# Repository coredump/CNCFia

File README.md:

# CNCFia

The idea with this board is to provide a *generic* shield/daughter card for 3.3V MCUs running CNC firmwares like GRBL (and its ports) and g2core. For that, instead of making a shield with specific sockets, we decided to provide a pin header that can be used to connect to different MCUs.

## Included capabilities

### Switches

There are six opto-isolated connectors for limit switches (X, Y, and Z Min/Max limits), a Probe connector and an extra opto-isolated connector to be used for any generic function, and five non-opto isolated ones to be used for external controls (Door security, Emergency Stop, etc).

The opto-isolated switches have an option to be powered by an entirely separated power source to provide full electrical isolation.

All the switches are pulled UP via 4.7kΩ resistors, intended to be used with NC (normally closed) switches connected to the GND, making it an active low signal. Take that in consideration when wiring/configuring the software.

### External driver control/level shifting

Support for nine voltage shifted outputs, mosfet (2n700X) driven. Enough to provide Step/Pulse/Enable signals for three external drivers (those usually have a 5V control voltage).

The mosfets connect the outputs to GND, so when wiring make sure to provide the 5V common wire to all positive (+) signals and the outputs to the negative (-) signals.

TODO example

## Jumper Settings

|  JP1  | Result                                                                                                   |
| :---: | -------------------------------------------------------------------------------------------------------- |
|  1-2  | 5V voltage for board functions will be provided by external power source connected to **EXTERNAL 5V IN** |
|  1-3  | 5V to board functions will be provided by the MCU 5V Pin connected to the controller input               |

## Connector Descriptions

TODO add descriptions and image

## Electrical notes

View this project on [CADLAB.io](https://cadlab.io/project/2459).

All calculations were made considering a 3.3V output from the driving MCU pins, while keeping the output currents under 10 mA, what should be safe for most of the MCUs around.

The 3904s driving the relays have a base current (Ib) of ~ 7.8 mA, that should be enough to saturate the transistor and provide the 78 mA needed by the relay coil.

The LTV-847s are used with typical values for Vf and If, according to datasheet specs.

The OPAMP output for the spindle can be regulated with a potentiometer and from the 3.3V PWM it can get values close to 11V with a 12V power source. Simulated circuit shows a 0.4s approximately time to get to the stable voltage.

## License, Copyright and disclaimers

Copyright Jose Junior <jose.junior@gmail.com> 2020.  

This documentation describes Open Hardware and is licensed under the
CERN OHL v. 1.2.  

You may redistribute and modify this documentation under the terms of the
[CERN OHL v.1.2.](http://ohwr.org/cernohl) This documentation is distributed
**WITHOUT ANY EXPRESS OR IMPLIED WARRANTY, INCLUDING OF
MERCHANTABILITY, SATISFACTORY QUALITY AND FITNESS FOR A
PARTICULAR PURPOSE**. Please see the CERN OHL v.1.2 for applicable
conditions.

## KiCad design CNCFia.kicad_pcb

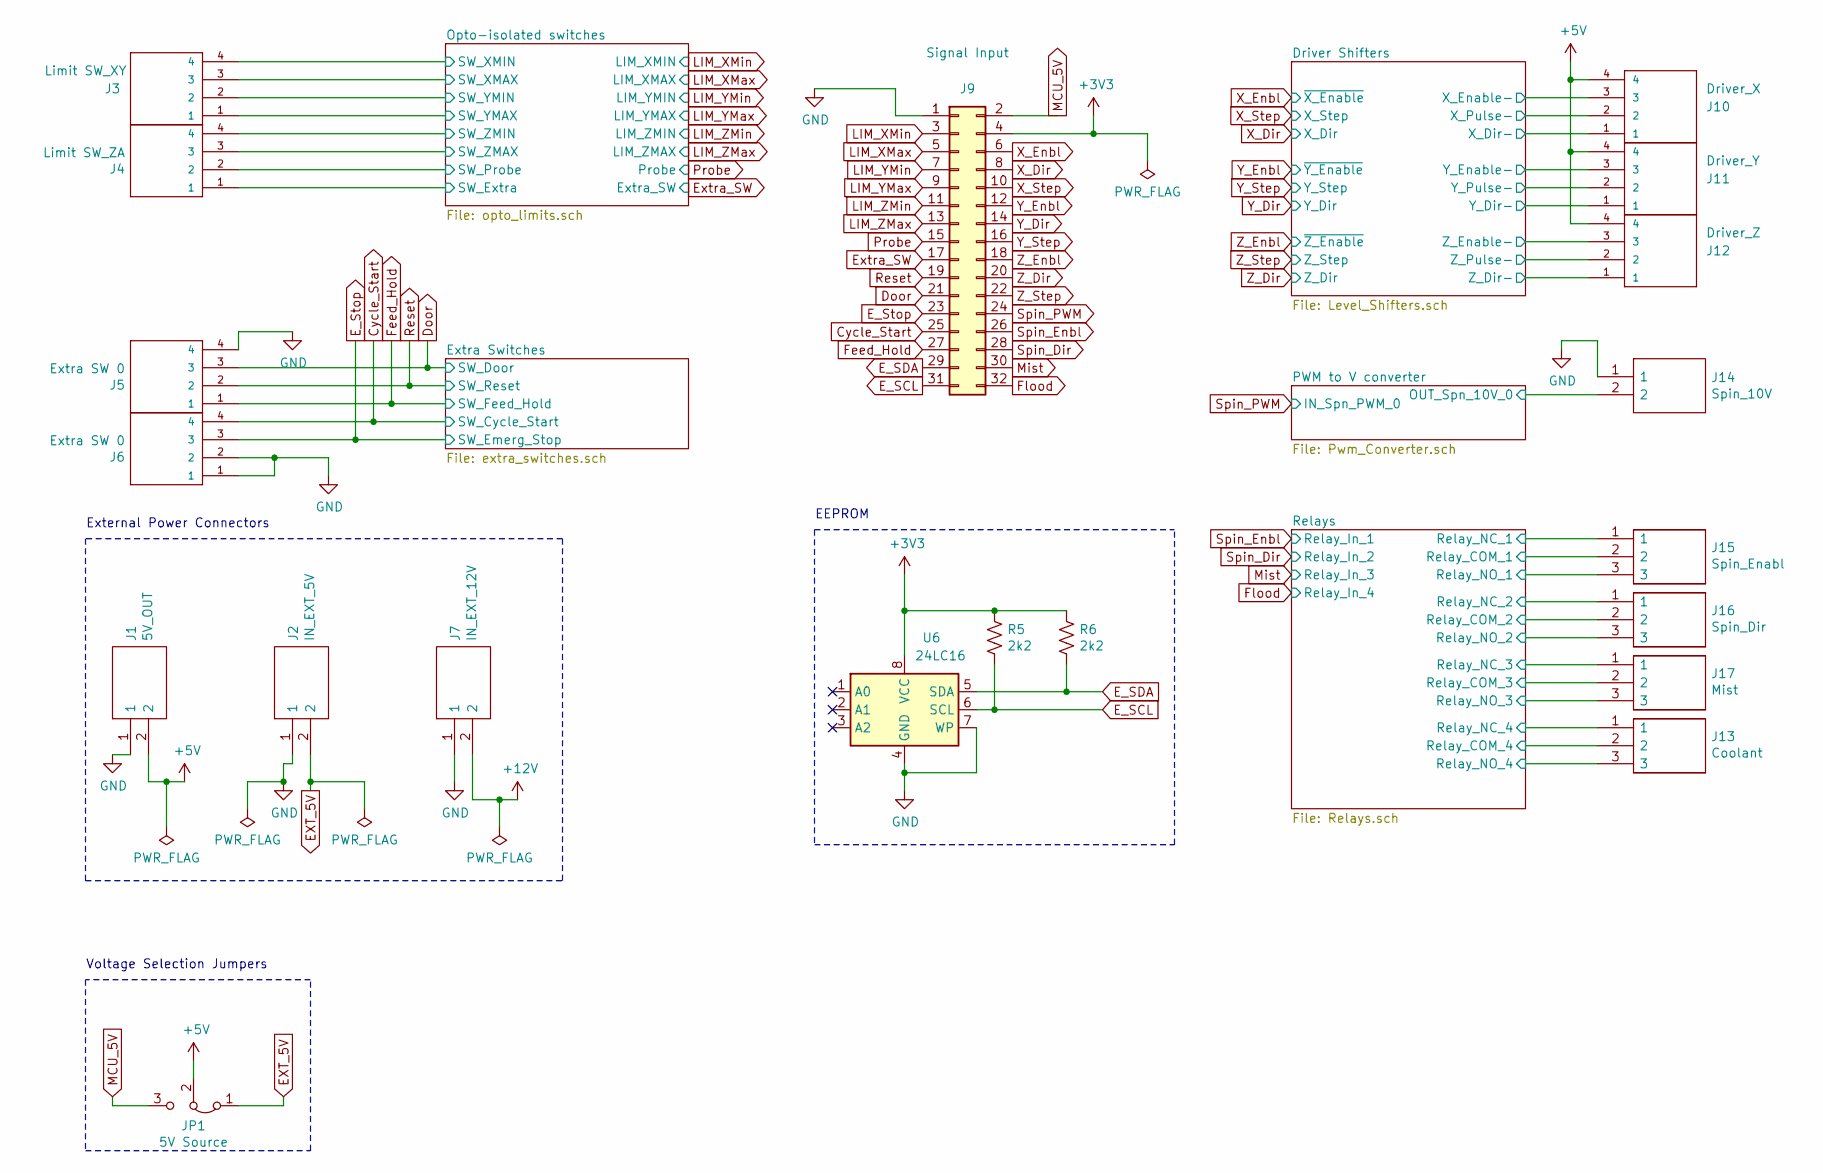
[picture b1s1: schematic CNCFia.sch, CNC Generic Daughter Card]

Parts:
J1: 5V_OUT; CUI_TBP02R2-381-02BE; Mouser Part Number 490-TB008A-508-02BE
J2: IN_EXT_5V; CUI_TBP02R2-381-02BE; Mouser Part Number 490-TB008A-508-02BE
J3: Limit SW_XY; CUI_TBP02R2-381-04BE; MPN TBP01R2-508-04BE; Digi-Key_PN 102-6424-ND
J4: Limit SW_ZA; CUI_TBP02R2-381-04BE; MPN TBP01R2-508-04BE; Digi-Key_PN 102-6424-ND
J5, J6: Extra SW 0; CUI_TBP02R2-381-04BE; MPN TBP01R2-508-04BE; Digi-Key_PN 102-6424-ND
J7: IN_EXT_12V; CUI_TBP02R2-381-02BE; Mouser Part Number 490-TB008A-508-02BE
J9: Signal Input; PinHeader_2x16_P2.54mm_Vertical; MPN 302-S401; Digi-Key_PN ED10529-ND
J10: Driver_X; CUI_TBP02R2-381-04BE; Mouser Part Number 490-TB008A-508-03BE
J11: Driver_Y; CUI_TBP02R2-381-04BE; Mouser Part Number 490-TB008A-508-03BE
J12: Driver_Z; CUI_TBP02R2-381-04BE; Mouser Part Number 490-TB008A-508-03BE
J13: Coolant; CUI_TBP02R2-381-03BE; Mouser Part Number 490-TB008A-508-03BE
J14: Spin_10V; CUI_TBP02R2-381-02BE; Mouser Part Number 490-TB008A-508-02BE
J15: Spin_Enabl; CUI_TBP02R2-381-03BE; Mouser Part Number 490-TB008A-508-03BE
J16: Spin_Dir; CUI_TBP02R2-381-03BE; Mouser Part Number 490-TB008A-508-03BE
J17: Mist; CUI_TBP02R2-381-03BE; Mouser Part Number 490-TB008A-508-03BE
JP1: 5V Source; PinHeader_1x03_P2.54mm_Vertical
R5, R6: 2k2; R_0805_2012Metric_Pad1.15x1.40mm_HandSolder; MPN CRGCQ1206F2K2; Digi-Key_PN A129814CT-ND
U6: 24LC16; SOIC-8_3.9x4.9mm_P1.27mm

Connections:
+5V: J1.2, J10.4, J11.4, J12.4, JP1.2 (C); also elsewhere on the board
+12V: J7.2; also elsewhere on the board
/OUT_Spn_10V_0: J14.2; also elsewhere on the board
/Relay_COM_1: J15.2; also elsewhere on the board
/Relay_COM_2: J16.2; also elsewhere on the board
/Relay_COM_3: J17.2; also elsewhere on the board
/Relay_COM_4: J13.2; also elsewhere on the board
/Relay_NC_1: J15.1; also elsewhere on the board
/Relay_NC_2: J16.1; also elsewhere on the board
/Relay_NC_3: J17.1; also elsewhere on the board
/Relay_NC_4: J13.1; also elsewhere on the board
/Relay_NO_1: J15.3; also elsewhere on the board
/Relay_NO_2: J16.3; also elsewhere on the board
/Relay_NO_3: J17.3; also elsewhere on the board
/Relay_NO_4: J13.3; also elsewhere on the board
/SW_Extra: J4.1; also elsewhere on the board
/SW_Probe: J4.2; also elsewhere on the board
/SW_XMAX: J3.3; also elsewhere on the board
/SW_XMIN: J3.4; also elsewhere on the board
/SW_YMAX: J3.1; also elsewhere on the board
/SW_YMIN: J3.2; also elsewhere on the board
/SW_ZMAX: J4.3; also elsewhere on the board
/SW_ZMIN: J4.4; also elsewhere on the board
/X_Dir-: J10.1; also elsewhere on the board
/X_Enable-: J10.3; also elsewhere on the board
/X_Pulse-: J10.2; also elsewhere on the board
/Y_Dir-: J11.1; also elsewhere on the board
/Y_Enable-: J11.3; also elsewhere on the board
/Y_Pulse-: J11.2; also elsewhere on the board
/Z_Dir-: J12.1; also elsewhere on the board
/Z_Enable-: J12.3; also elsewhere on the board
/Z_Pulse-: J12.2; also elsewhere on the board
Cycle_Start: J6.4, J9.25; also elsewhere on the board
Door: J5.3, J9.21; also elsewhere on the board
EXT_5V: J2.2, JP1.1 (A)
E_SCL: J9.31, R5.2, U6.6 (SCL)
E_SDA: J9.29, R6.2, U6.5 (SDA)
E_Stop: J6.3, J9.23; also elsewhere on the board
Extra_SW: J9.17; also elsewhere on the board
Feed_Hold: J5.1, J9.27; also elsewhere on the board
Flood: J9.32; also elsewhere on the board
GND: J1.1, J2.1, J5.4, J6.1, J6.2, J7.1, J9.1, J14.1, U6.4 (GND), U6.7 (WP); also elsewhere on the board
LIM_XMax: J9.5; also elsewhere on the board
LIM_XMin: J9.3; also elsewhere on the board
LIM_YMax: J9.9; also elsewhere on the board
LIM_YMin: J9.7; also elsewhere on the board
LIM_ZMax: J9.13; also elsewhere on the board
LIM_ZMin: J9.11; also elsewhere on the board
MCU_5V: J9.2, JP1.3 (B)
Mist: J9.30; also elsewhere on the board
Probe: J9.15; also elsewhere on the board
Reset: J5.2, J9.19; also elsewhere on the board
Spin_Dir: J9.28; also elsewhere on the board
Spin_Enbl: J9.26; also elsewhere on the board
Spin_PWM: J9.24; also elsewhere on the board
X_Dir: J9.8; also elsewhere on the board
X_Enbl: J9.6; also elsewhere on the board
X_Step: J9.10; also elsewhere on the board
Y_Dir: J9.14; also elsewhere on the board
Y_Enbl: J9.12; also elsewhere on the board
Y_Step: J9.16; also elsewhere on the board
Z_Dir: J9.20; also elsewhere on the board
Z_Enbl: J9.18; also elsewhere on the board
Z_Step: J9.22; also elsewhere on the board

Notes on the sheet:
External Power Connectors
Voltage Selection Jumpers
EEPROM

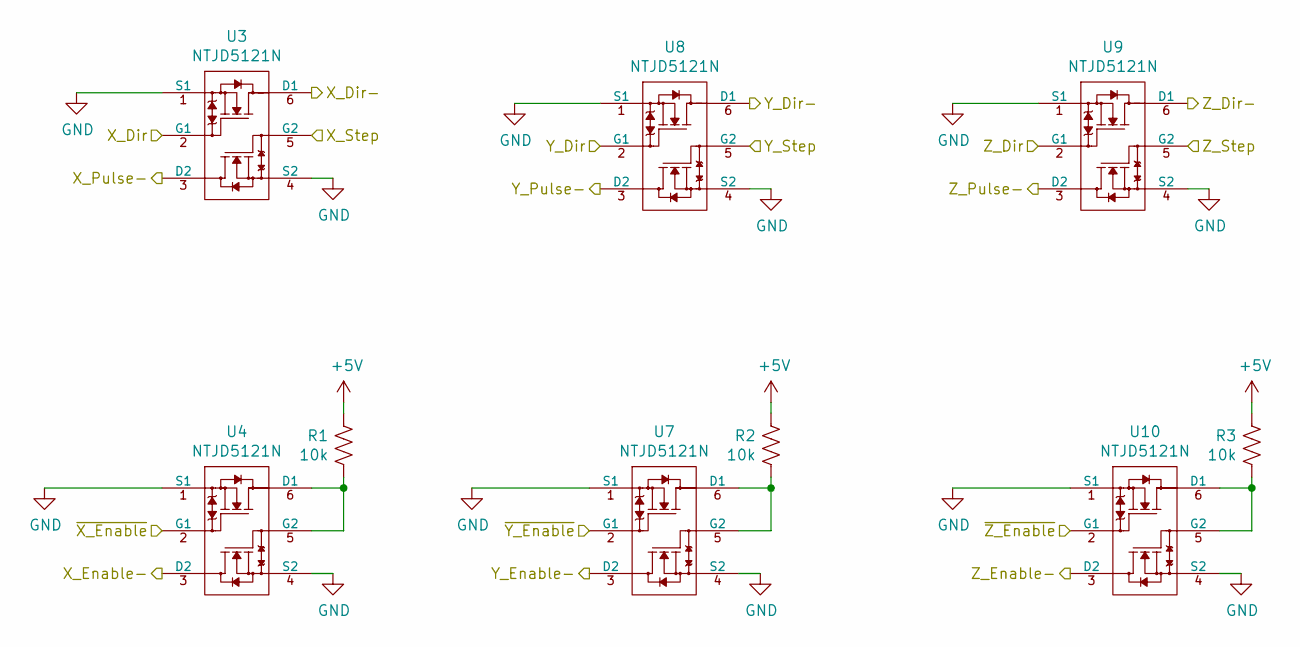
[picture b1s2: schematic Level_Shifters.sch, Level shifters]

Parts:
R1, R2, R3: 10k; R_0805_2012Metric_Pad1.15x1.40mm_HandSolder
U3, U4, U7, U8, U9, U10: NTJD5121N; SOT-363_SC-70-6

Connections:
+5V: R1.1, R2.1, R3.1; also elsewhere on the board
/X_Dir-: U3.6 (D1); also elsewhere on the board
/X_Enable-: U4.3 (D2); also elsewhere on the board
/X_Pulse-: U3.3 (D2); also elsewhere on the board
/Y_Dir-: U8.6 (D1); also elsewhere on the board
/Y_Enable-: U7.3 (D2); also elsewhere on the board
/Y_Pulse-: U8.3 (D2); also elsewhere on the board
/Z_Dir-: U9.6 (D1); also elsewhere on the board
/Z_Enable-: U10.3 (D2); also elsewhere on the board
/Z_Pulse-: U9.3 (D2); also elsewhere on the board
GND: U3.1 (S1), U3.4 (S2), U4.1 (S1), U4.4 (S2), U7.1 (S1), U7.4 (S2), U8.1 (S1), U8.4 (S2), U9.1 (S1), U9.4 (S2), U10.1 (S1), U10.4 (S2); also elsewhere on the board
unnamed: R1.2, U4.5 (G2), U4.6 (D1)
unnamed: R2.2, U7.5 (G2), U7.6 (D1)
unnamed: R3.2, U10.5 (G2), U10.6 (D1)
X_Dir: U3.2 (G1); also elsewhere on the board
X_Enbl: U4.2 (G1); also elsewhere on the board
X_Step: U3.5 (G2); also elsewhere on the board
Y_Dir: U8.2 (G1); also elsewhere on the board
Y_Enbl: U7.2 (G1); also elsewhere on the board
Y_Step: U8.5 (G2); also elsewhere on the board
Z_Dir: U9.2 (G1); also elsewhere on the board
Z_Enbl: U10.2 (G1); also elsewhere on the board
Z_Step: U9.5 (G2); also elsewhere on the board

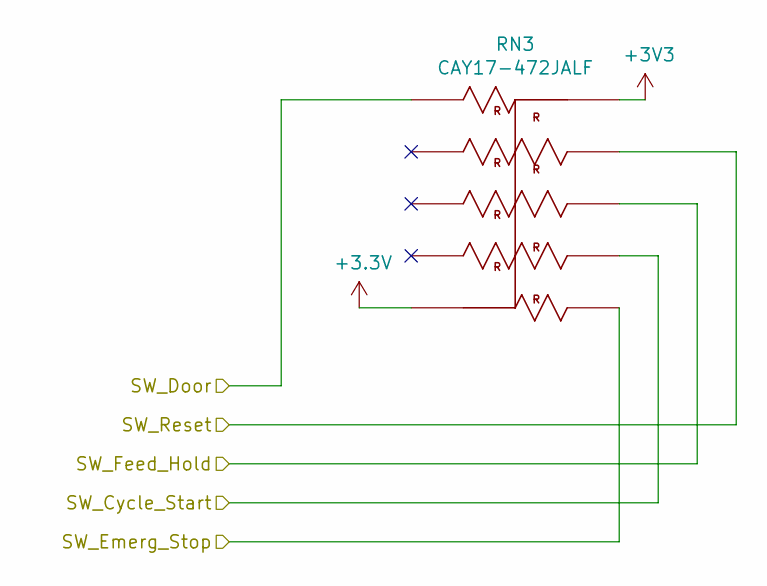
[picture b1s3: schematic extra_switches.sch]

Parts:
RN3: CAY17-472JALF; RESCAXS64P320X160X60-10N; MPN CAY17-472JALF; Digi-Key_PN CAY17-472JALFCT-ND

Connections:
Cycle_Start: RN3.2; also elsewhere on the board
Door: RN3.6; also elsewhere on the board
E_Stop: RN3.1; also elsewhere on the board
Feed_Hold: RN3.3; also elsewhere on the board
Reset: RN3.4; also elsewhere on the board

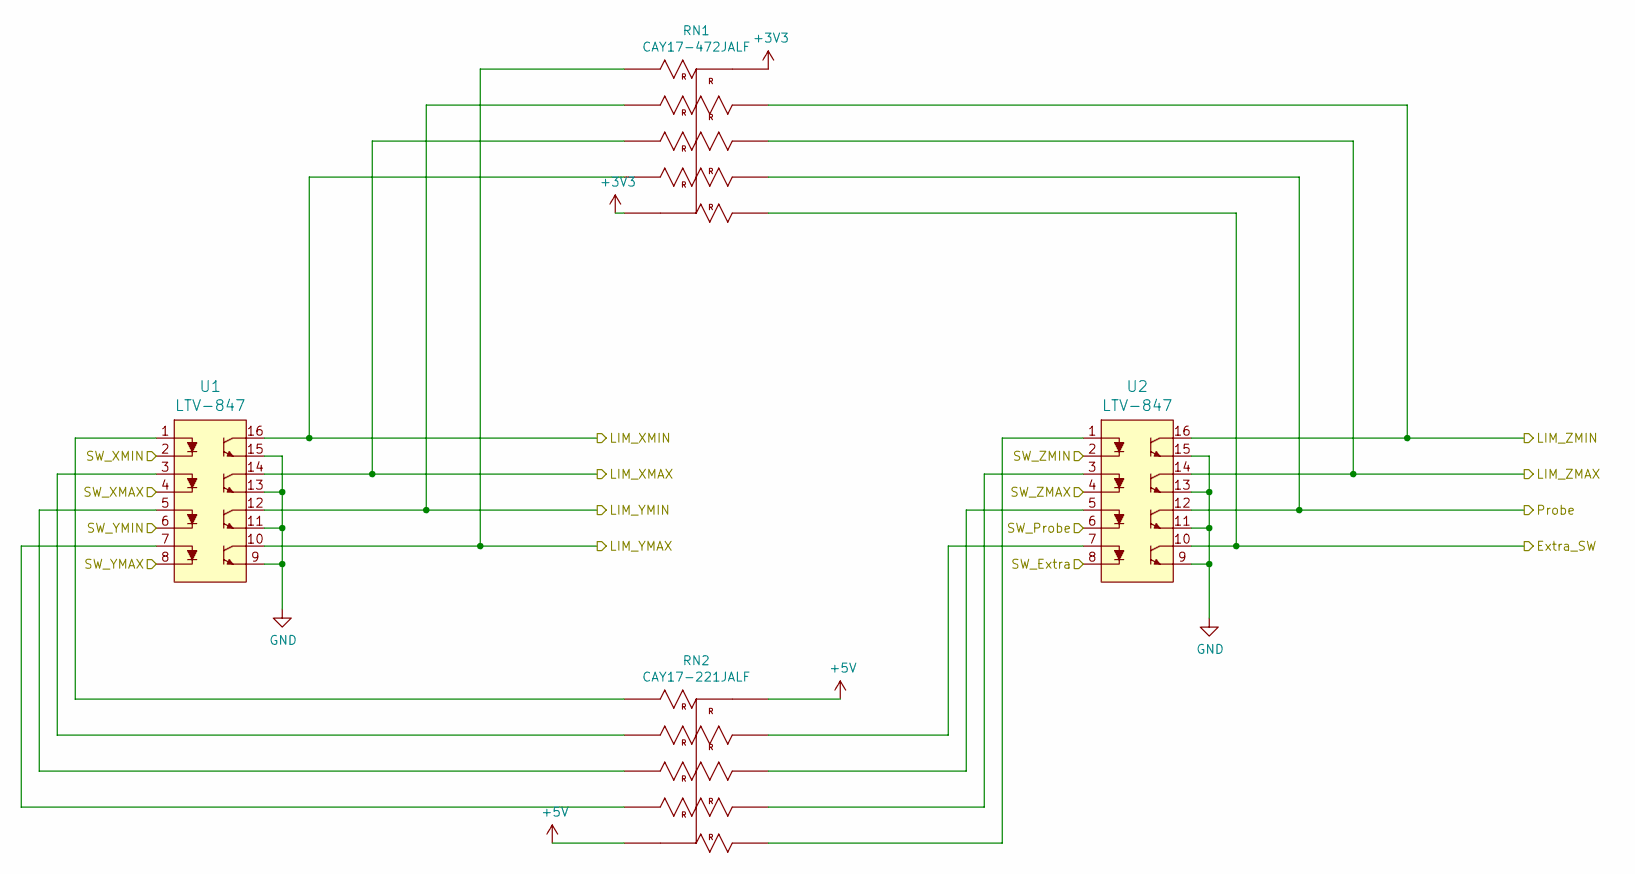
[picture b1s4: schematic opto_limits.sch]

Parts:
RN1: CAY17-472JALF; RESCAXS64P320X160X60-10N; MPN CAY17-472JALF; Digi-Key_PN CAY17-472JALFCT-ND
RN2: CAY17-221JALF; RESCAXS64P320X160X60-10N; MPN CAY17-221JALF; Digi-Key_PN CAY17-221JALF-ND
U1, U2: LTV-847; SOIC254P1016X460-16N; MPN LTV-847S; Digi-Key_PN 160-1371-5-ND

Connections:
+5V: RN2.5, RN2.10; also elsewhere on the board
/SW_Extra: U2.8; also elsewhere on the board
/SW_Probe: U2.6; also elsewhere on the board
/SW_XMAX: U1.4; also elsewhere on the board
/SW_XMIN: U1.2; also elsewhere on the board
/SW_YMAX: U1.8; also elsewhere on the board
/SW_YMIN: U1.6; also elsewhere on the board
/SW_ZMAX: U2.4; also elsewhere on the board
/SW_ZMIN: U2.2; also elsewhere on the board
Extra_SW: RN1.1, U2.10; also elsewhere on the board
GND: U1.9, U1.11, U1.13, U1.15, U2.9, U2.11, U2.13, U2.15; also elsewhere on the board
LIM_XMax: RN1.8, U1.14; also elsewhere on the board
LIM_XMin: RN1.9, U1.16; also elsewhere on the board
LIM_YMax: RN1.6, U1.10; also elsewhere on the board
LIM_YMin: RN1.7, U1.12; also elsewhere on the board
LIM_ZMax: RN1.3, U2.14; also elsewhere on the board
LIM_ZMin: RN1.4, U2.16; also elsewhere on the board
unnamed: RN2.1, U2.1
unnamed: RN2.2, U2.3
unnamed: RN2.3, U2.5
unnamed: RN2.4, U2.7
unnamed: RN2.6, U1.1
unnamed: RN2.7, U1.3
unnamed: RN2.8, U1.5
unnamed: RN2.9, U1.7
Probe: RN1.2, U2.12; also elsewhere on the board

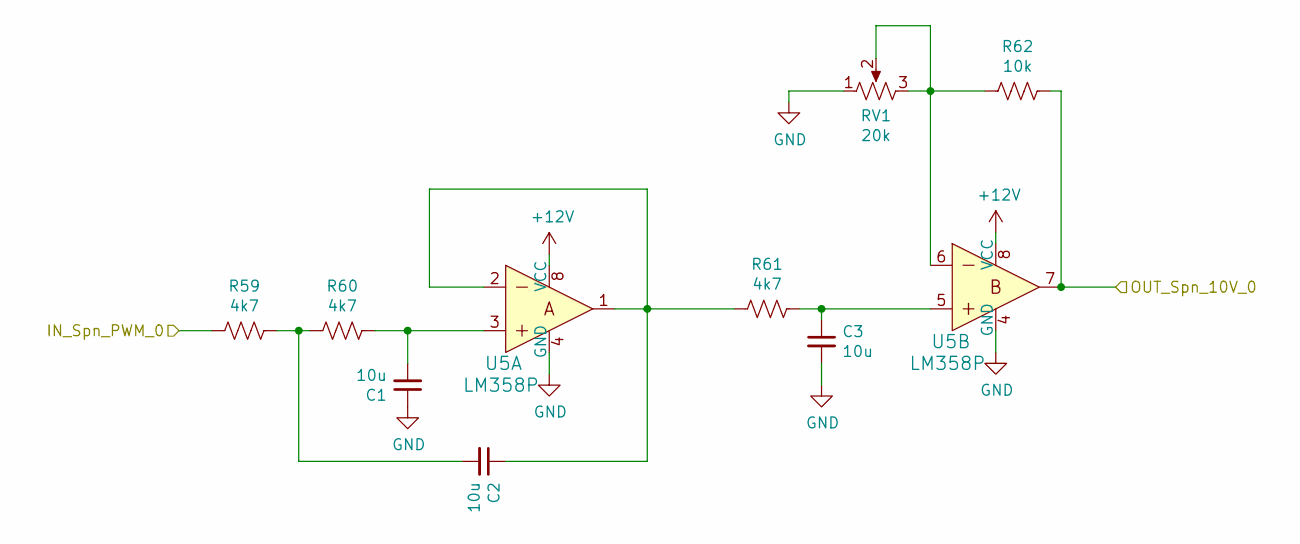
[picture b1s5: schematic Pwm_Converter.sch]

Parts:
C1, C2, C3: 10u; C_1206_3216Metric_Pad1.42x1.75mm_HandSolder; MPN CL31A106MQHNNNE; Digi-Key_PN 1276-3045-1-ND
R59, R60, R61: 4k7; R_0805_2012Metric_Pad1.15x1.40mm_HandSolder; MPN CRGCQ1206F4K7; Digi-Key_PN A129818CT-ND
R62: 10k; R_0805_2012Metric_Pad1.15x1.40mm_HandSolder; MPN CRGCQ1206J10K; Digi-Key_PN A130183CT-ND
RV1: 20k; Potentiometer_ACP_CA6-H2,5_Horizontal; MPN N6L50T0C-203; Digi-Key_PN 1993-1217-ND
U5: LM358P; SOIC-8_3.9x4.9mm_P1.27mm; MPN LM358ADRG4; Digi-Key_PN 296-31667-1-ND

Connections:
+12V: U5.8 (VCC); also elsewhere on the board
/OUT_Spn_10V_0: R62.1, U5.7; also elsewhere on the board
GND: C1.1, C3.2, RV1.1, U5.4 (GND); also elsewhere on the board
unnamed: C1.2, R60.1, U5.3
unnamed: C2.1, R61.2, U5.1, U5.2
unnamed: C2.2, R59.1, R60.2
unnamed: C3.1, R61.1, U5.5
unnamed: R62.2, RV1.2, RV1.3, U5.6
Spin_PWM: R59.2; also elsewhere on the board

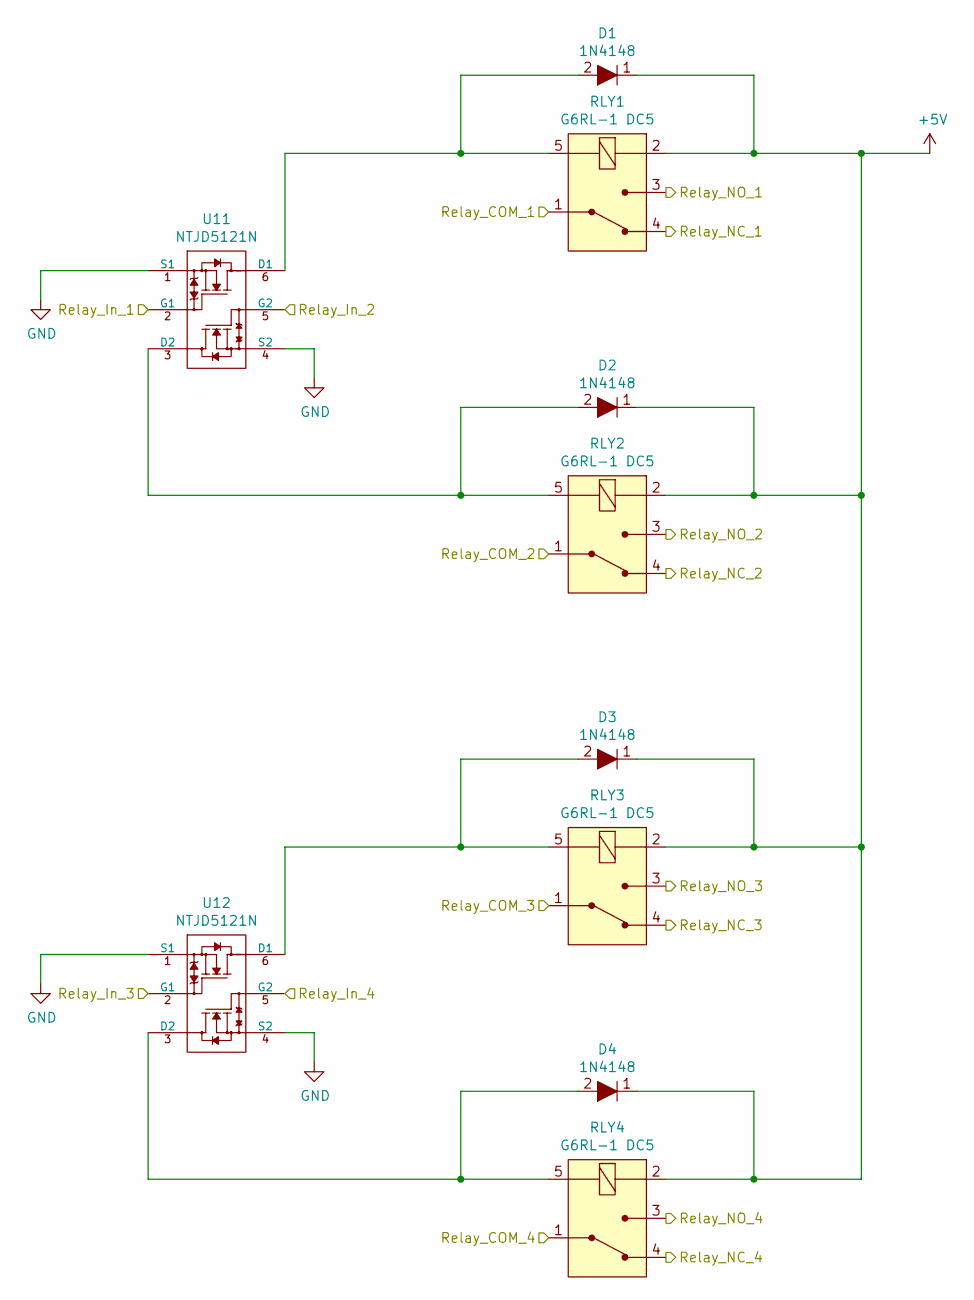
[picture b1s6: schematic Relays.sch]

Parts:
D1, D2, D3, D4: 1N4148; D_SOD-123; MPN MMSD4148T1G; Digi-Key_PN MMSD4148T1GOSCT-ND
RLY1, RLY2, RLY3, RLY4: G6RL-1 DC5; RELAY_G6RL-1_5VDC; MPN G6RL-1 DC5; Digi-Key_PN Z2902-ND
U11, U12: NTJD5121N; SOT-363_SC-70-6

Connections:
+5V: D1.1, D2.1, D3.1, D4.1, RLY1.2 (COIL), RLY2.2 (COIL), RLY3.2 (COIL), RLY4.2 (COIL); also elsewhere on the board
/Relay_COM_1: RLY1.1 (COM); also elsewhere on the board
/Relay_COM_2: RLY2.1 (COM); also elsewhere on the board
/Relay_COM_3: RLY3.1 (COM); also elsewhere on the board
/Relay_COM_4: RLY4.1 (COM); also elsewhere on the board
/Relay_NC_1: RLY1.4 (NC); also elsewhere on the board
/Relay_NC_2: RLY2.4 (NC); also elsewhere on the board
/Relay_NC_3: RLY3.4 (NC); also elsewhere on the board
/Relay_NC_4: RLY4.4 (NC); also elsewhere on the board
/Relay_NO_1: RLY1.3 (NO); also elsewhere on the board
/Relay_NO_2: RLY2.3 (NO); also elsewhere on the board
/Relay_NO_3: RLY3.3 (NO); also elsewhere on the board
/Relay_NO_4: RLY4.3 (NO); also elsewhere on the board
Flood: U12.5 (G2); also elsewhere on the board
GND: U11.1 (S1), U11.4 (S2), U12.1 (S1), U12.4 (S2); also elsewhere on the board
Mist: U12.2 (G1); also elsewhere on the board
unnamed: D1.2, RLY1.5 (COIL), U11.6 (D1)
unnamed: D2.2, RLY2.5 (COIL), U11.3 (D2)
unnamed: D3.2, RLY3.5 (COIL), U12.6 (D1)
unnamed: D4.2, RLY4.5 (COIL), U12.3 (D2)
Spin_Dir: U11.5 (G2); also elsewhere on the board
Spin_Enbl: U11.2 (G1); also elsewhere on the board

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
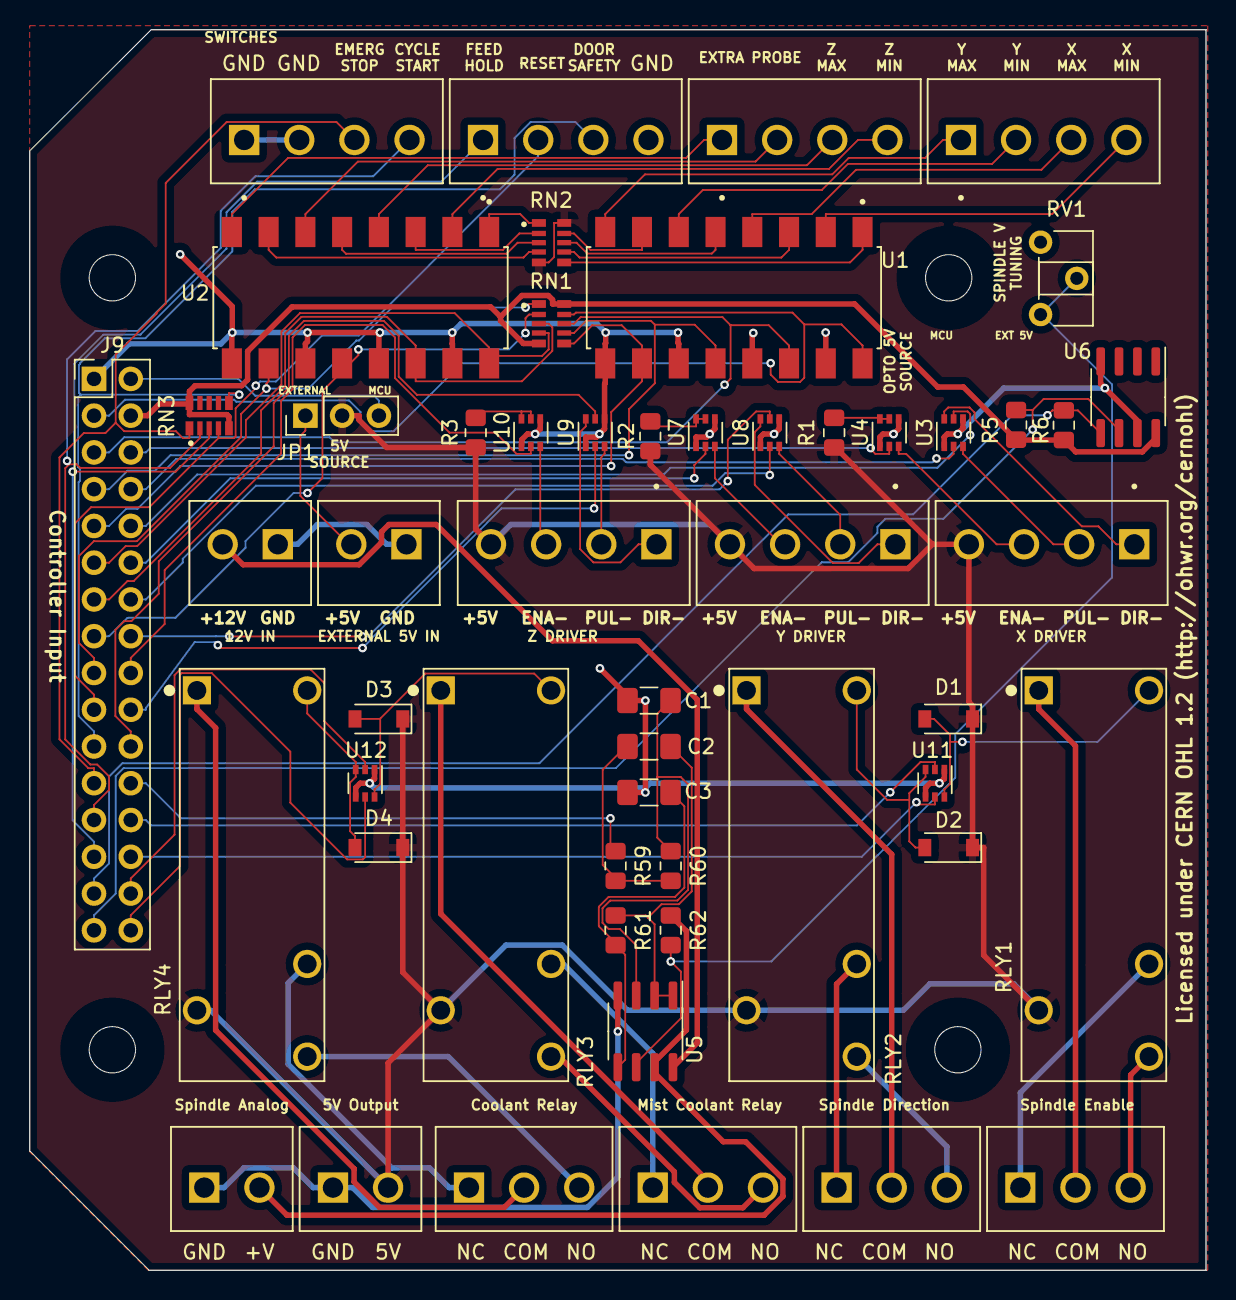
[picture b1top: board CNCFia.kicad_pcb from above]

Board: 2 copper layers, 81.3 x 85.7 mm, 57 parts (0 on the bottom side), 85 nets.

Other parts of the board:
M1, M2, M3, M4: MountingHole_3.2mm_M3

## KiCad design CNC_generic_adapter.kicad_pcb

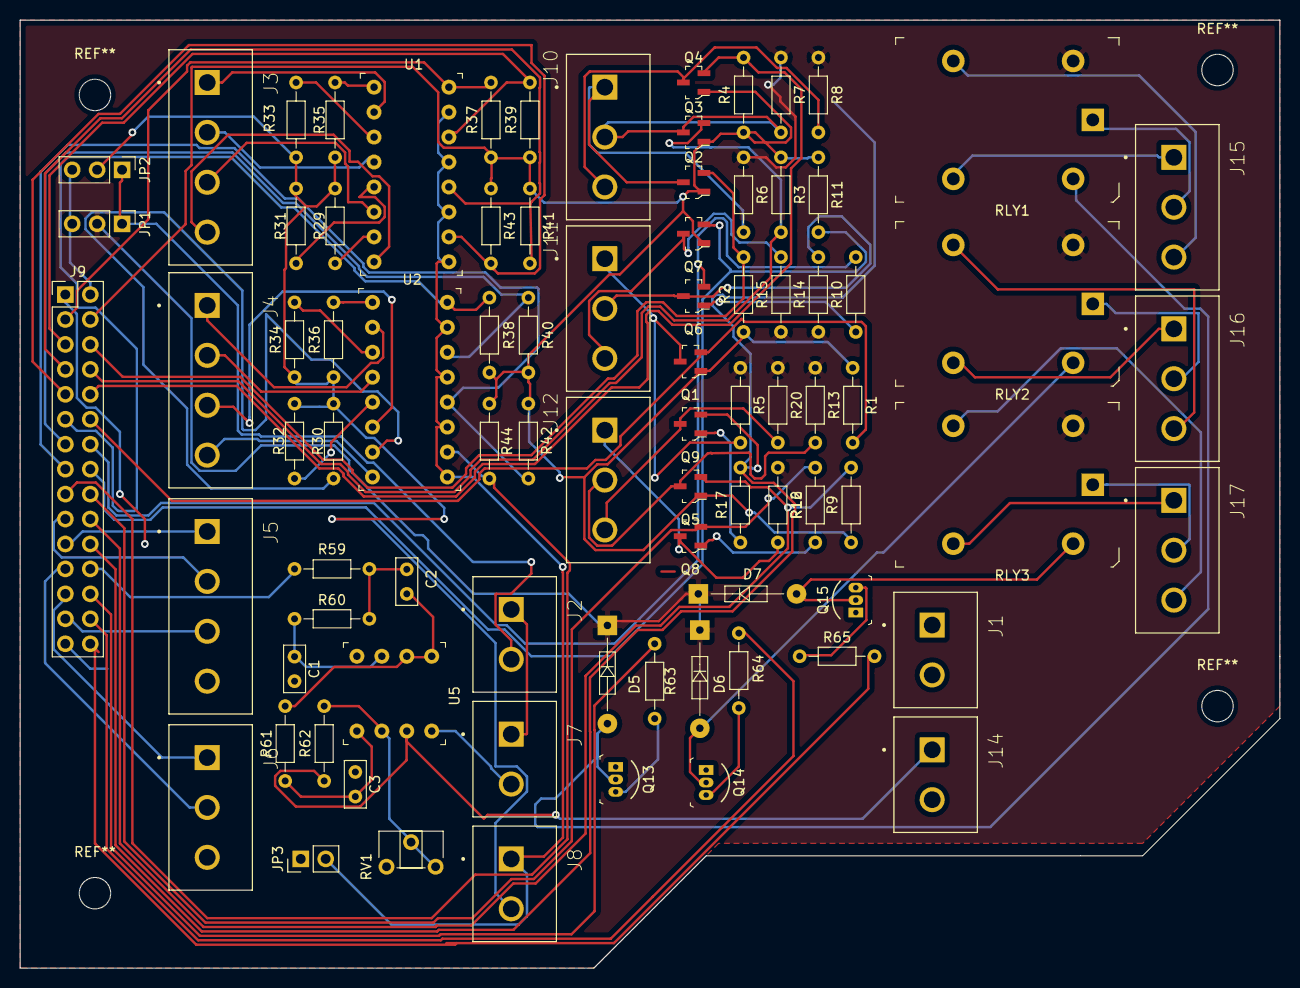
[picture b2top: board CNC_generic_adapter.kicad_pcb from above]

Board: 2 copper layers, 128.3 x 96.5 mm, 85 parts (0 on the bottom side), 83 nets.

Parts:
C1, C2, C3: 10u; C_Rect_L4.6mm_W2.0mm_P2.50mm_MKS02_FKP02
D5, D6, D7: 1N4148; Diode_DO-35_P10mm
J1: GND; CUI_TBP01R2-508-02BE
J2: EXT_5V; CUI_TBP01R2-508-02BE
J3: Limit SW_XY; CUI_TBP01R2-508-04BE
J4: Limit SW_ZA; CUI_TBP01R2-508-04BE
J5: Extra SW 0; CUI_TBP01R2-508-04BE
J6: Extra SW 1; CUI_TBP01R2-508-03BE
J7: EXT_12V; CUI_TBP01R2-508-02BE
J8: OPTO_5V; CUI_TBP01R2-508-02BE
J9: Signal Input; PinHeader_2x15_P2.54mm_Vertical
J10: Driver_X; CUI_TBP01R2-508-03BE
J11: Driver_Y; CUI_TBP01R2-508-03BE
J12: Driver_Z; CUI_TBP01R2-508-03BE
J14: Spin_10V; CUI_TBP01R2-508-02BE
J15: Relay_1; CUI_TBP01R2-508-03BE
J16: Relay_2; CUI_TBP01R2-508-03BE
J17: Relay_3; CUI_TBP01R2-508-03BE
JP1: 5V Source; PinHeader_1x03_P2.54mm_Vertical
JP2: Opto_V_Source; PinHeader_1x03_P2.54mm_Vertical
JP3: Opto_GND_Source; PinHeader_1x02_P2.54mm_Vertical
Q1, Q2, Q3, Q4, Q5, Q6, Q7, Q8, Q9: BSS138; SOT-23-3
Q13, Q14, Q15: 2N3904; TO-92-3
R1, R2, R3, R4, R5, R6, R7, R8, R9, R10, R11, R12, R13, R14, R15, R16, R17, R20, R62: 10k; R_Axial_DIN0204_L3.6mm_D1.6mm_P7.62mm_Horizontal
R29, R30, R31, R32, R33, R34, R35, R36: 220R; R_Axial_DIN0204_L3.6mm_D1.6mm_P7.62mm_Horizontal
R37, R38, R39, R40, R41, R42, R43, R44: 4K7; R_Axial_DIN0204_L3.6mm_D1.6mm_P7.62mm_Horizontal
R59, R60, R61: 4k7; R_Axial_DIN0204_L3.6mm_D1.6mm_P7.62mm_Horizontal
R63, R64, R65: 2k2; R_Axial_DIN0204_L3.6mm_D1.6mm_P7.62mm_Horizontal
RLY1, RLY2, RLY3: G5LE-14_DC5; Relay_THT_G5LE-14
RV1: 20k; Potentiometer_ACP_CA6-H2,5_Horizontal
U1, U2: LTV-847; Socket_DIP-16_7.62mm_Conn
U5: LM358P; SOCKET_DIP-8_7.62mm_Conn

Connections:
+3V3: J9.4, Q1.1, Q2.1, Q3.1, Q4.1, Q5.1, Q7.1, R1.1, R2.1, R3.1, R4.1, R9.1, R11.1, R37.1, R38.1, R39.1, R40.1, R41.1, R42.1, R43.1, R44.1
+5V: D5.1, D6.1, D7.1, JP1.2, R5.1, R6.1, R7.1, R8.1, R13.1, R14.1, R15.1, R16.1, R20.1, RLY1.2, RLY2.2, RLY3.2
+12V: J7.2, U5.8
/Level Shifters/HV_1: J10.1, Q2.3, R6.2
/Level Shifters/HV_2: J10.2, Q3.3, R7.2
/Level Shifters/HV_3: J10.3, Q4.3, R8.2
/Level Shifters/HV_4: J11.1, Q1.3, R5.2
/Level Shifters/HV_5: J11.2, Q6.3, R14.2
/Level Shifters/HV_6: J11.3, Q7.3, R15.2
/Level Shifters/HV_7: J12.1, Q8.3, R16.2
/Level Shifters/HV_8: J12.2, Q5.3, R13.2
/Level Shifters/HV_9: J12.3, Q9.3, R20.2
/Opto-isolated switches/SW_Extra: J4.4, U2.8
/Opto-isolated switches/SW_Probe: J4.3, U2.6
/Opto-isolated switches/SW_XMAX: J3.2, U1.4
/Opto-isolated switches/SW_XMIN: J3.1, U1.2
/Opto-isolated switches/SW_YMAX: J3.4, U1.8
/Opto-isolated switches/SW_YMIN: J3.3, U1.6
/Opto-isolated switches/SW_ZMAX: J4.2, U2.4
/Opto-isolated switches/SW_ZMIN: J4.1, U2.2
/PWM to V converter/OUT_Spn_10V_0: J14.1, R62.1, U5.7
/Relays/Relay_COM_1: J15.2, RLY1.1
/Relays/Relay_COM_2: J16.2, RLY2.1
/Relays/Relay_COM_3: J17.2, RLY3.1
/Relays/Relay_NC_1: J15.1, RLY1.4
/Relays/Relay_NC_2: J16.1, RLY2.4
/Relays/Relay_NC_3: J17.1, RLY3.4
/Relays/Relay_NO_1: J15.3, RLY1.3
/Relays/Relay_NO_2: J16.3, RLY2.3
/Relays/Relay_NO_3: J17.3, RLY3.3
Cycle_Start: J6.1, J9.25
Door: J5.1, J9.21
EXT_5V: J2.2, JP1.1, JP2.1
E_Stop: J6.2, J9.23
Extra_SW: J9.17, R44.2, U2.10
Feed_Hold: J5.3, J9.27
GND: C1.1, C3.2, J1.1, J1.2, J2.1, J5.4, J6.3, J7.1, J9.1, J9.29, J14.2, JP3.1, Q13.1, Q14.1, Q15.1, RV1.1, U5.4
IN_Relay_1: J9.26, R63.2
IN_Relay_2: J9.28, R64.2
IN_Relay_3: J9.30, R65.2
LIM_XMax: J9.5, R39.2, U1.14
LIM_XMin: J9.3, R37.2, U1.16
LIM_YMax: J9.9, R43.2, U1.10
LIM_YMin: J9.7, R41.2, U1.12
LIM_ZMax: J9.13, R40.2, U2.14
LIM_ZMin: J9.11, R38.2, U2.16
LV_1: J9.6, Q2.2, R2.2
LV_2: J9.8, Q3.2, R3.2
LV_3: J9.10, Q4.2, R4.2
LV_4: J9.12, Q1.2, R1.2
LV_5: J9.14, Q6.2, R10.2
LV_6: J9.16, Q7.2, R11.2
LV_7: J9.18, Q8.2, R12.2
LV_8: J9.20, Q5.2, R9.2
LV_9: J9.22, Q9.2, R17.2
MCU_5V: J9.2, JP1.3, JP2.3
unnamed: C1.2, R60.1, U5.3
unnamed: C2.1, R61.2, U5.1, U5.2
unnamed: C2.2, R59.1, R60.2
unnamed: C3.1, R61.1, U5.5
unnamed: D5.2, Q13.2, RLY1.5
unnamed: D6.2, Q14.2, RLY2.5
unnamed: D7.2, Q15.2, RLY3.5
unnamed: Q6.1, R10.1
unnamed: Q8.1, R12.1
unnamed: Q9.1, R17.1
unnamed: Q13.3, R63.1
unnamed: Q14.3, R64.1
unnamed: Q15.3, R65.1
unnamed: R29.2, U1.7
unnamed: R30.2, U2.7
unnamed: R31.2, U1.5
unnamed: R32.2, U2.5
unnamed: R33.2, U1.3
unnamed: R34.2, U2.3
unnamed: R35.2, U1.1
unnamed: R36.2, U2.1
unnamed: R62.2, RV1.2, RV1.3, U5.6
OPTO_5V: J8.2, JP2.2, R29.1, R30.1, R31.1, R32.1, R33.1, R34.1, R35.1, R36.1
OPTO_GND: J8.1, JP3.2, U1.9, U1.11, U1.13, U1.15, U2.9, U2.11, U2.13, U2.15
Probe: J9.15, R42.2, U2.12
Reset: J5.2, J9.19
SPIN_PWM: J9.24, R59.2

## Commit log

2020-02-05 Backlink to CADLAB.io has been added.
2020-02-05 Adding cache.lib for cadlab
2020-02-05 Renamed Kicad Project, cleanup
2020-02-05 Remove unecessary modules config
2020-02-05 Flatten submodules into repo
2020-02-05 Even more flattening for Cadlab
2020-02-05 Remove extraneous Sparkfun stuff
2020-02-05 Before autorouting
2020-02-06 Pre-SMD
2020-02-07 Makes it SMD based, with smaller connectors
2020-02-07 Vertical mounted version
2020-02-07 New routing
2020-02-07 Fixing schematic symbols
2020-02-07 Added some more comments to sheets
2020-02-10 Changed wrong GND for limit switches
2020-02-14 New libs and 3d/footprints
2020-02-14 Adds a sheet for pull up resistors on extra sw
2020-02-14 Change mosfets and resistors to arrays
2020-02-14 Made it more neat and organized
2020-02-14 Fixing Symbols
2020-02-14 More symbols fixed
2020-02-14 Simplify the power options
2020-02-14 Simplify the power options again
2020-02-14 Added License
2020-02-15 Change the License to CERN OHL and add required docs
2020-02-15 Cosmetic and text changes

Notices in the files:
CNCFia.kicad_pcb:
Licensed under CERN OHL 1.2 (http://ohwr.org/cernohl)
